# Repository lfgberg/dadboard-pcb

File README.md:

# This has not yet been tested, and firmware has not yet been pushed to qmk/via, pcb may or may not function as intended

# Dadboard PCB

PCB designed for [enwash](https://github.com/enwash) and [tesla.tech's]() [Dadboard]() Split 75%

## Renders

## Production

Download the [latest release of the production files](https://github.com/lfgberg/dadboard-pcb/releases), and submit them to a PCB manufacturer like JLCPCB or PCBWay.

## Assembly

Required:
* 1x EC11 Alps Rotary Encoder
* 2x TRRS-PJ-320A Ports

Optional:
* 92 Kailh hotswap sockets

## Author
[Lfgberg](https://github.com/lfgberg)
<br>

## License
[Attribution-NonCommercial-ShareAlike 4.0 International](https://creativecommons.org/licenses/by-nc-sa/4.0/)

This is not available for commercial use, contact [Lfgberg](https://github.com/lfgberg) for more information.

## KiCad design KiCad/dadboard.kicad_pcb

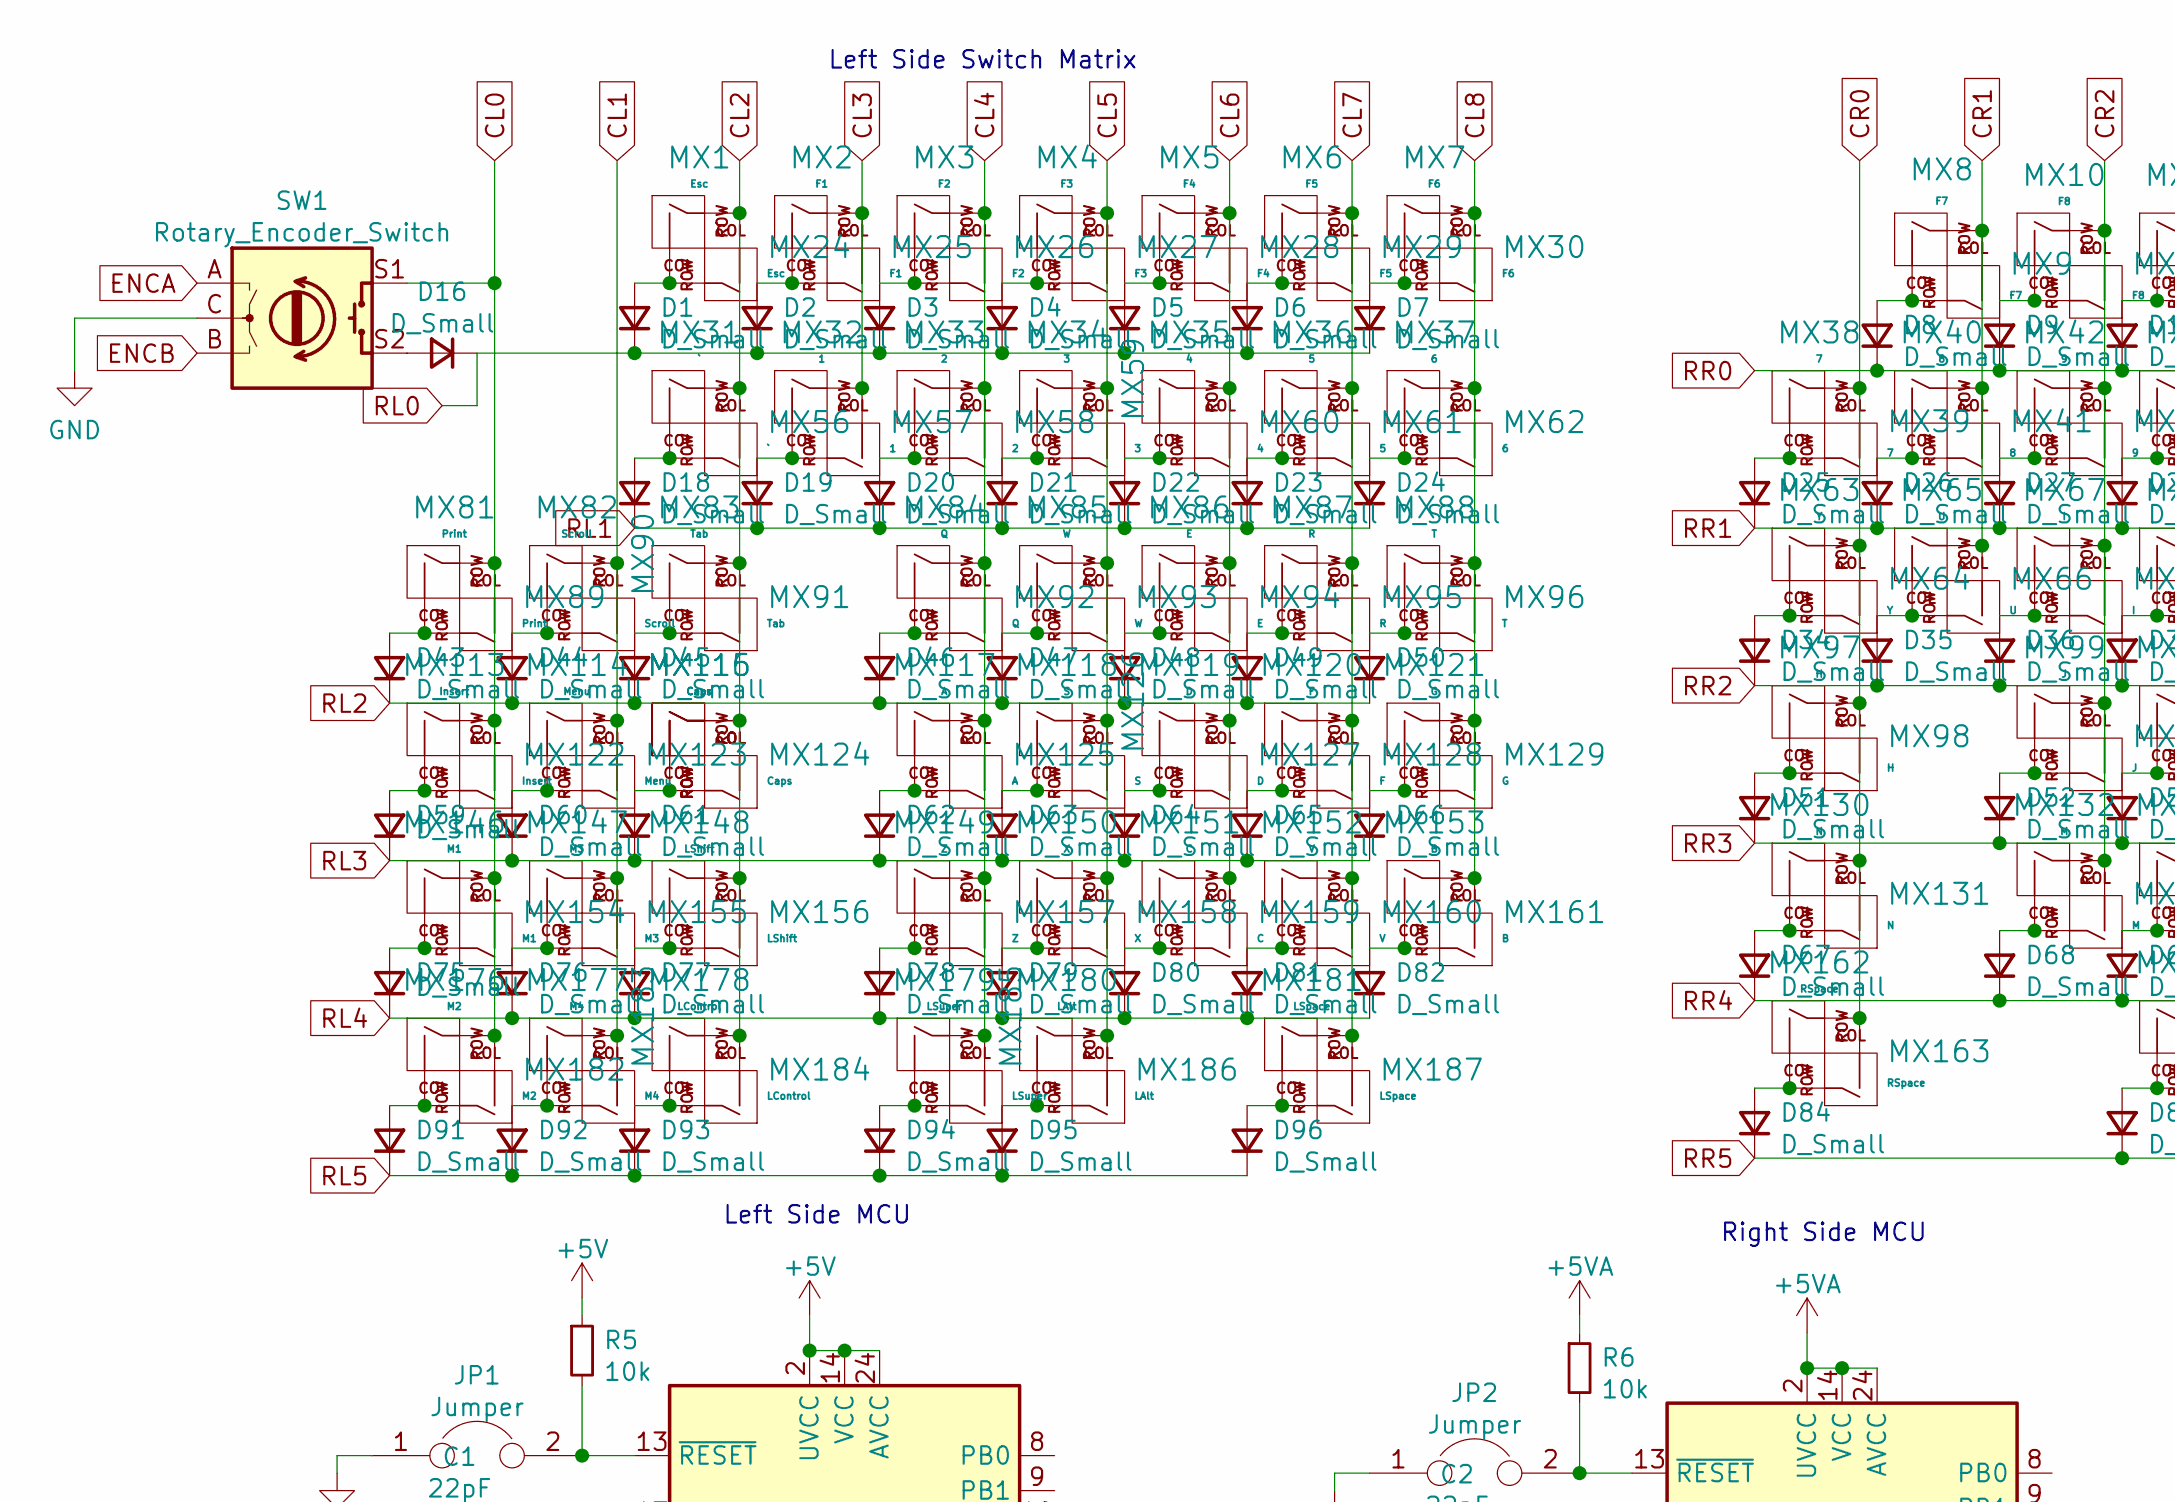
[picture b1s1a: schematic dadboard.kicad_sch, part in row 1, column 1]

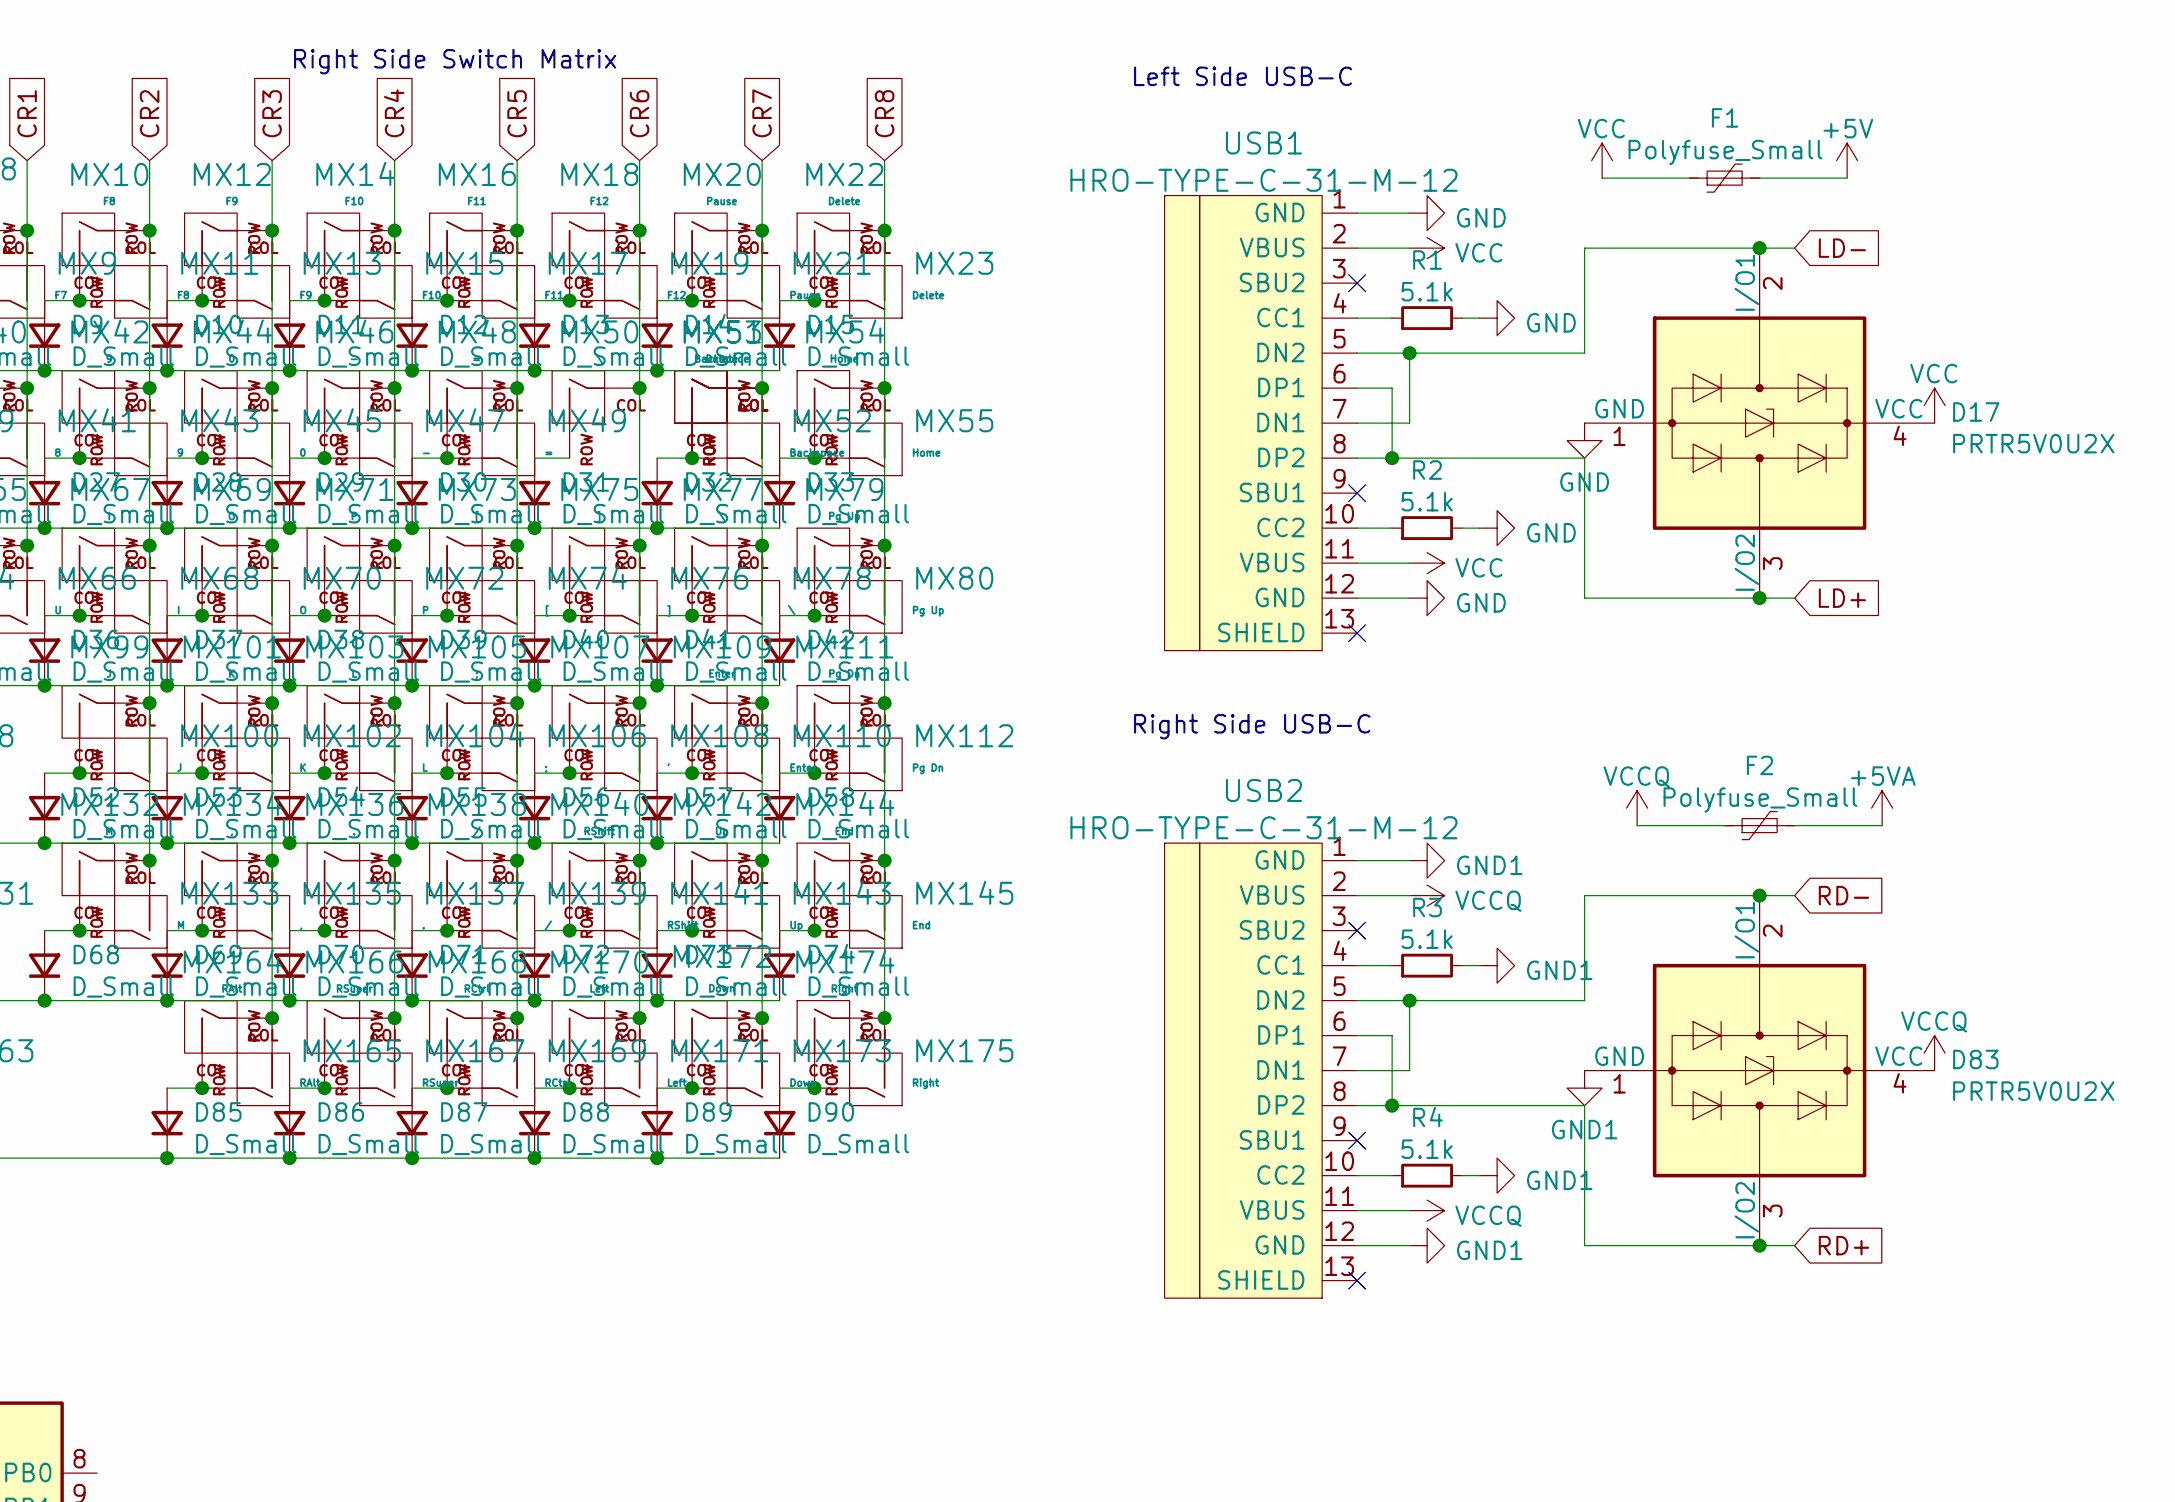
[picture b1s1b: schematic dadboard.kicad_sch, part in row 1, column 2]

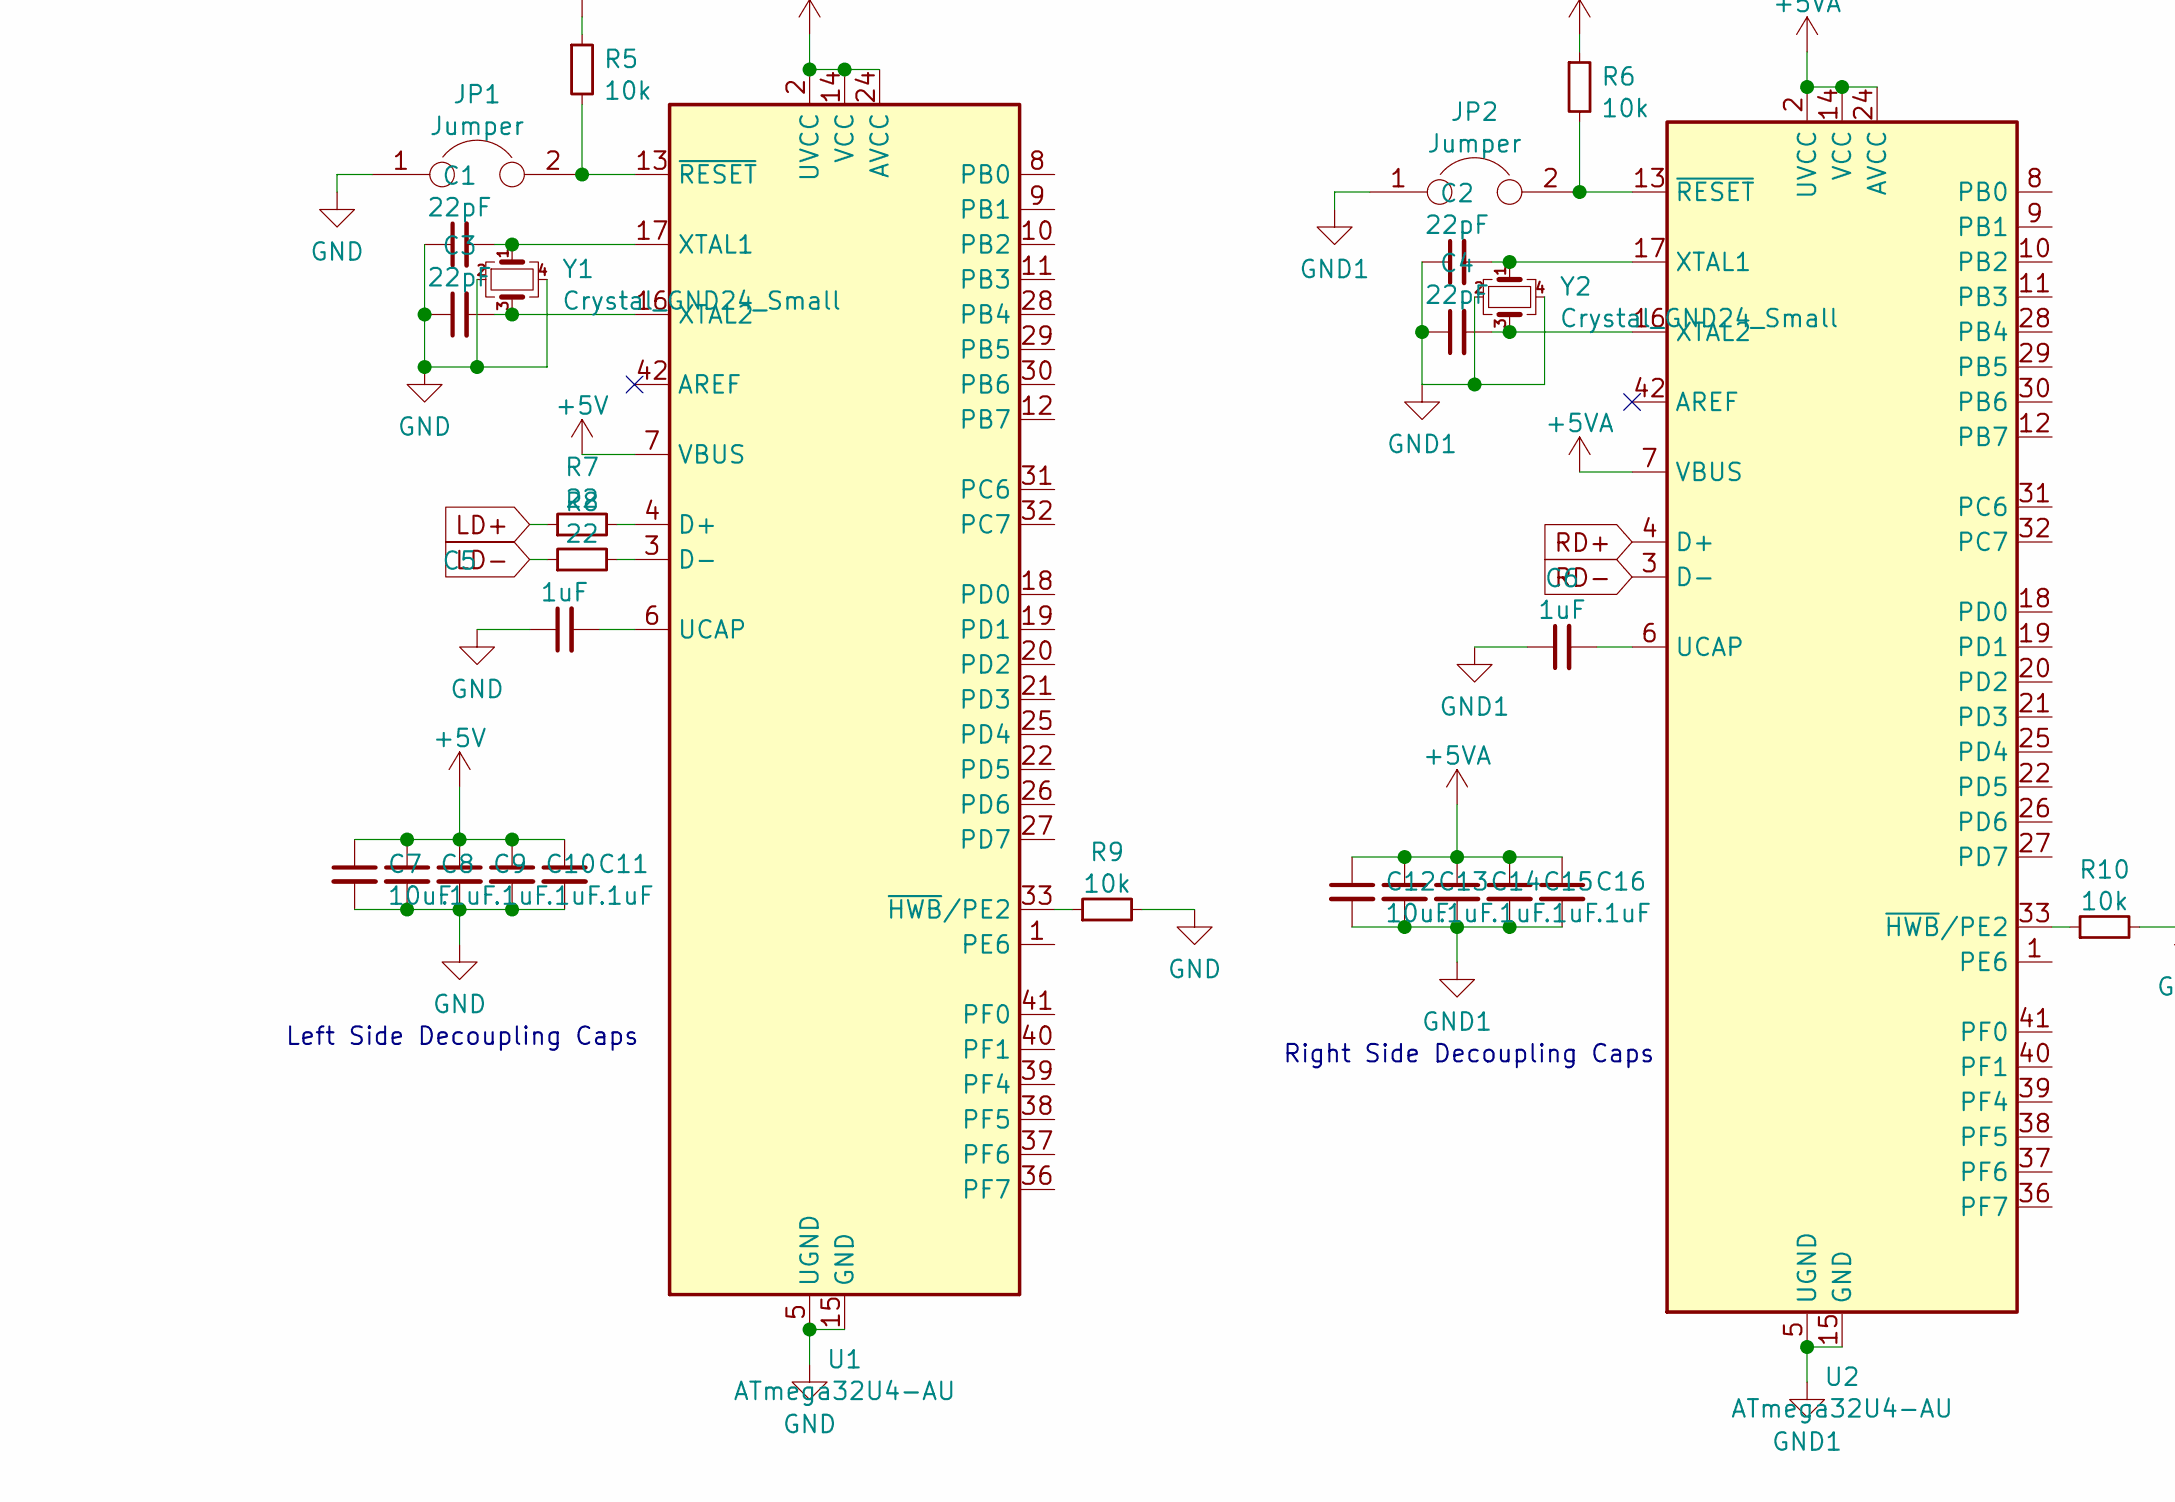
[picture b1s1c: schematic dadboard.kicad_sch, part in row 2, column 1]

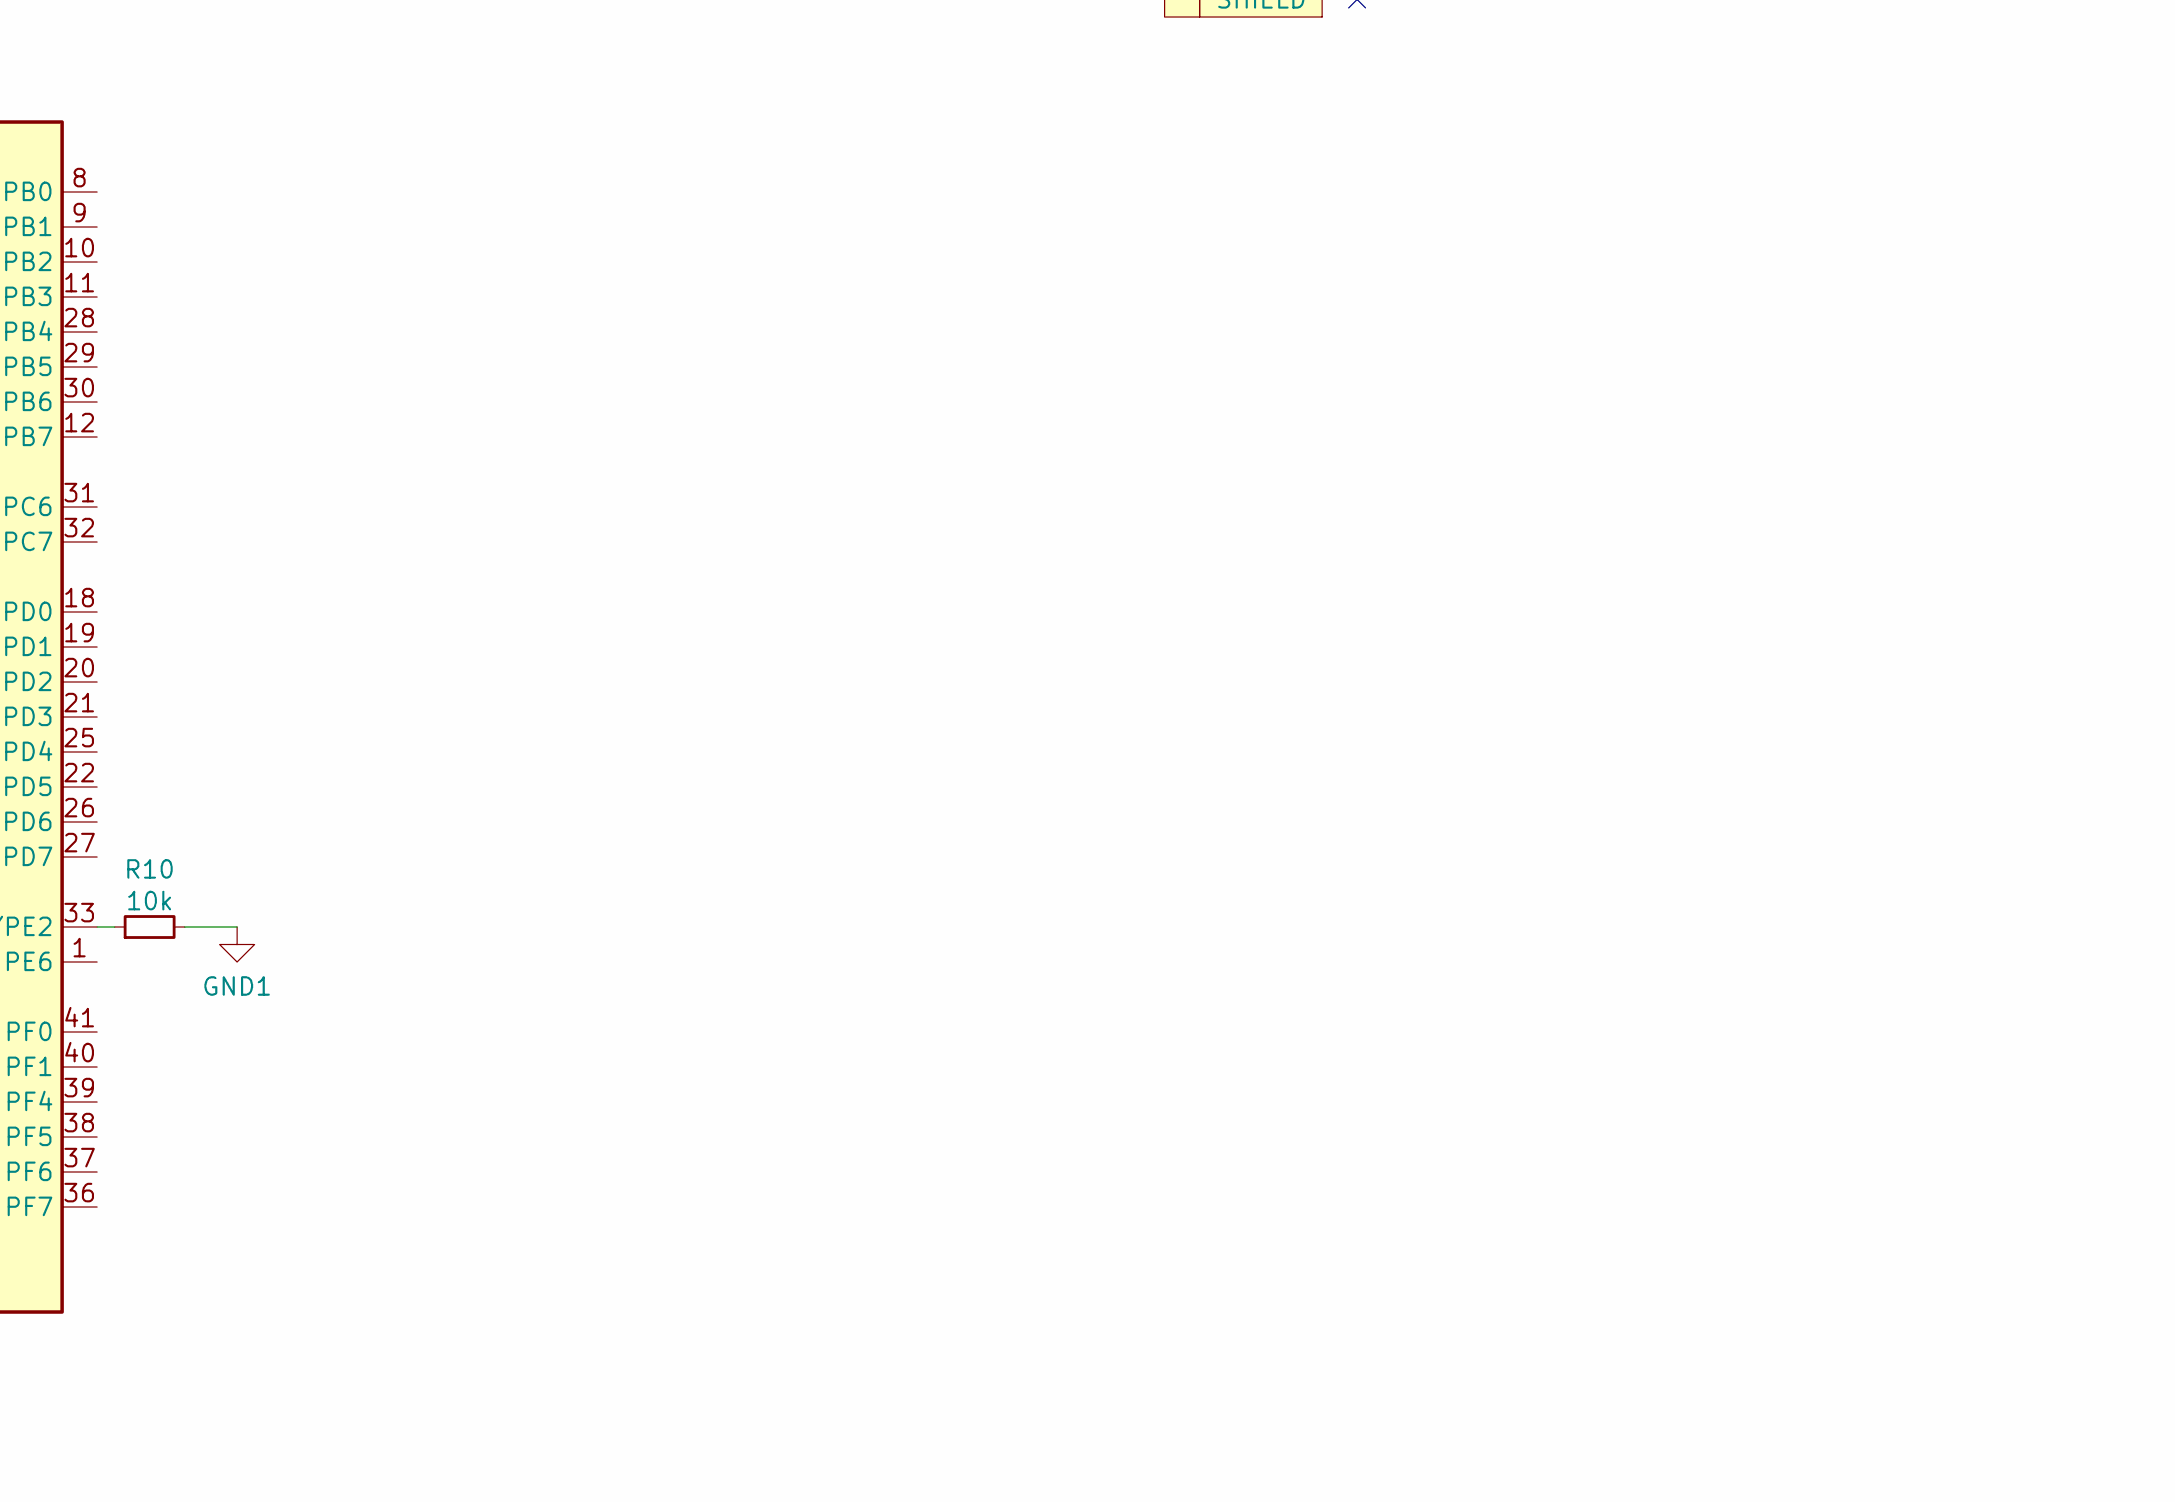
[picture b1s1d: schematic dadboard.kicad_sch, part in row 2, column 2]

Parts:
C1, C2, C3, C4: 22pF; C_0805_2012Metric
C5, C6: 1uF; C_0805_2012Metric
C7, C12: 10uF; C_0805_2012Metric
C8, C9, C10, C11, C13, C14, C15, C16: .1uF; C_0805_2012Metric
D1, D2, D3, D4, D5, D6, D7, D8, D9, D10, D11, D12, D13, D14, D15, D16, D18, D19, D20, D21, D22, D23, D24, D25, D26, D27, D28, D29, D30, D31, D32, D33, D34, D35, D36, D37, D38, D39, D40, D41, D42, D43, D44, D45, D46, D47, D48, D49, D50, D51, D52, D53, D54, D55, D56, D57, D58, D59, D60, D61, D62, D63, D64, D65, D66, D67, D68, D69, D70, D71, D72, D73, D74, D75, D76, D77, D78, D79, D80, D81, D82, D84, D85, D86, D87, D88, D89, D90, D91, D92, D93, D94, D95, D96: D_Small; D_SOD-123-Pretty
D17, D83: PRTR5V0U2X; SOT-143
F1, F2: Polyfuse_Small; Fuse_0805_2012Metric
JP1, JP2: Jumper; ResetJumper
MX1: Esc; MXOnly-1U-NoLED
MX2: F1; MXOnly-1U-NoLED
MX3: F2; MXOnly-1U-NoLED
MX4: F3; MXOnly-1U-NoLED
MX5: F4; MXOnly-1U-NoLED
MX6: F5; MXOnly-1U-NoLED
MX7: F6; MXOnly-1U-NoLED
MX8: F7; MXOnly-1U-NoLED
MX9: F7; MXOnly-1U-Hotswap
MX10: F8; MXOnly-1U-NoLED
MX11: F8; MXOnly-1U-Hotswap
MX12: F9; MXOnly-1U-NoLED
MX13: F9; MXOnly-1U-Hotswap
MX14: F10; MXOnly-1U-NoLED
MX15: F10; MXOnly-1U-Hotswap
MX16: F11; MXOnly-1U-NoLED
MX17: F11; MXOnly-1U-Hotswap
MX18: F12; MXOnly-1U-NoLED
MX19: F12; MXOnly-1U-Hotswap
MX20: Pause; MXOnly-1U-NoLED
MX21: Pause; MXOnly-1U-Hotswap
MX22, MX53: Delete; MXOnly-1U-NoLED
MX23: Delete; MXOnly-1U-Hotswap
MX24: Esc; MXOnly-1U-Hotswap
MX25: F1; MXOnly-1U-Hotswap
MX26: F2; MXOnly-1U-Hotswap
MX27: F3; MXOnly-1U-Hotswap
MX28: F4; MXOnly-1U-Hotswap
MX29: F5; MXOnly-1U-Hotswap
MX30: F6; MXOnly-1U-Hotswap
MX31: `; MXOnly-1U-NoLED
MX32: 1; MXOnly-1U-NoLED
MX33: 2; MXOnly-1U-NoLED
MX34: 3; MXOnly-1U-NoLED
MX35: 4; MXOnly-1U-NoLED
MX36: 5; MXOnly-1U-NoLED
MX37: 6; MXOnly-1U-NoLED
MX38: 7; MXOnly-1U-NoLED
MX39: 7; MXOnly-1U-Hotswap
MX40: 8; MXOnly-1U-NoLED
MX41: 8; MXOnly-1U-Hotswap
MX42: 9; MXOnly-1U-NoLED
MX43: 9; MXOnly-1U-Hotswap
MX44: 0; MXOnly-1U-NoLED
MX45: 0; MXOnly-1U-Hotswap
MX46: -; MXOnly-1U-NoLED
MX47: -; MXOnly-1U-Hotswap
MX48: =; MXOnly-1U-NoLED
MX49: =; MXOnly-1U-Hotswap
MX50: \; MXOnly-1U-NoLED
MX51: Backspace; MXOnly-2U-NoLED
MX52: Backspace; MXOnly-2U-Hotswap
MX54: Home; MXOnly-1U-NoLED
MX55: Home; MXOnly-1U-Hotswap
MX56: `; MXOnly-1U-Hotswap
MX57: 1; MXOnly-1U-Hotswap
MX58: 2; MXOnly-1U-Hotswap
MX59: 3; MXOnly-1U-Hotswap
MX60: 4; MXOnly-1U-Hotswap
MX61: 5; MXOnly-1U-Hotswap
MX62: 6; MXOnly-1U-Hotswap
MX63: Y; MXOnly-1U-NoLED
MX64: Y; MXOnly-1U-Hotswap
MX65: U; MXOnly-1U-NoLED
MX66: U; MXOnly-1U-Hotswap
MX67: I; MXOnly-1U-NoLED
MX68: I; MXOnly-1U-Hotswap
MX69: O; MXOnly-1U-NoLED
MX70: O; MXOnly-1U-Hotswap
MX71: P; MXOnly-1U-NoLED
MX72: P; MXOnly-1U-Hotswap
MX73: [; MXOnly-1U-NoLED
MX74: [; MXOnly-1U-Hotswap
MX75: ]; MXOnly-1U-NoLED
MX76: ]; MXOnly-1U-Hotswap
MX77: \; MXOnly-1.5U-NoLED
MX78: \; MXOnly-1.5U-Hotswap
MX79: Pg Up; MXOnly-1U-NoLED
MX80: Pg Up; MXOnly-1U-Hotswap
MX81: Print; MXOnly-1U-NoLED
MX82: Scroll; MXOnly-1U-NoLED
MX83: Tab; MXOnly-1.5U-NoLED
MX84: Q; MXOnly-1U-NoLED
MX85: W; MXOnly-1U-NoLED
MX86: E; MXOnly-1U-NoLED
MX87: R; MXOnly-1U-NoLED
MX88: T; MXOnly-1U-NoLED
MX89: Print; MXOnly-1U-Hotswap
MX90: Scroll; MXOnly-1U-Hotswap
MX91: Tab; MXOnly-1.5U-Hotswap
MX92: Q; MXOnly-1U-Hotswap
MX93: W; MXOnly-1U-Hotswap
MX94: E; MXOnly-1U-Hotswap
MX95: R; MXOnly-1U-Hotswap
MX96: T; MXOnly-1U-Hotswap
MX97: H; MXOnly-1U-NoLED
MX98: H; MXOnly-1U-Hotswap
MX99: J; MXOnly-1U-NoLED
MX100: J; MXOnly-1U-Hotswap
MX101: K; MXOnly-1U-NoLED
MX102: K; MXOnly-1U-Hotswap
MX103: L; MXOnly-1U-NoLED
MX104: L; MXOnly-1U-Hotswap
MX105: ;; MXOnly-1U-NoLED
MX106: ;; MXOnly-1U-Hotswap
MX107: '; MXOnly-1U-NoLED
MX108: '; MXOnly-1U-Hotswap
MX109: Enter; MXOnly-2.25U-NoLED
MX110: Enter; MXOnly-2.25U-Hotswap
MX111: Pg Dn; MXOnly-1U-NoLED
MX112: Pg Dn; MXOnly-1U-Hotswap
MX113: Insert; MXOnly-1U-NoLED
MX114: Menu; MXOnly-1U-NoLED
MX115: Caps; MXOnly-1.75U-NoLED
MX116: Caps; MXOnly-1.25U-NoLED
MX117: A; MXOnly-1U-NoLED
MX118: S; MXOnly-1U-NoLED
MX119: D; MXOnly-1U-NoLED
MX120: F; MXOnly-1U-NoLED
MX121: G; MXOnly-1U-NoLED
MX122: Insert; MXOnly-1U-Hotswap
MX123: Menu; MXOnly-1U-Hotswap
MX124: Caps; MXOnly-1.75U-Hotswap
MX125: A; MXOnly-1U-Hotswap
MX126: S; MXOnly-1U-Hotswap
MX127: D; MXOnly-1U-Hotswap
MX128: F; MXOnly-1U-Hotswap
MX129: G; MXOnly-1U-Hotswap
MX130: N; MXOnly-1U-NoLED
MX131: N; MXOnly-1U-Hotswap
MX132: M; MXOnly-1U-NoLED
MX133: M; MXOnly-1U-Hotswap
MX134: ,; MXOnly-1U-NoLED
MX135: ,; MXOnly-1U-Hotswap
MX136: .; MXOnly-1U-NoLED
MX137: .; MXOnly-1U-Hotswap
MX138: /; MXOnly-1U-NoLED
MX139: /; MXOnly-1U-Hotswap
MX140: RShift; MXOnly-1.75U-NoLED
MX141: RShift; MXOnly-1.75U-Hotswap
MX142: Up; MXOnly-1U-NoLED
MX143: Up; MXOnly-1U-Hotswap
MX144: End; MXOnly-1U-NoLED
MX145: End; MXOnly-1U-Hotswap
MX146: M1; MXOnly-1U-NoLED
MX147: M3; MXOnly-1U-NoLED
MX148: LShift; MXOnly-2.25U-NoLED
MX149: Z; MXOnly-1U-NoLED
MX150: X; MXOnly-1U-NoLED
MX151: C; MXOnly-1U-NoLED
MX152: V; MXOnly-1U-NoLED
MX153: B; MXOnly-1U-NoLED
MX154: M1; MXOnly-1U-Hotswap
MX155: M3; MXOnly-1U-Hotswap
MX156: LShift; MXOnly-2.25U-Hotswap
MX157: Z; MXOnly-1U-Hotswap
MX158: X; MXOnly-1U-Hotswap
MX159: C; MXOnly-1U-Hotswap
MX160: V; MXOnly-1U-Hotswap
MX161: B; MXOnly-1U-Hotswap
MX162: RSpace; MXOnly-3U-ReversedStabilizers-NoLED
MX163: RSpace; MXOnly-1U-Hotswap
MX164: RAlt; MXOnly-1U-NoLED
MX165: RAlt; MXOnly-1U-Hotswap
MX166: RSuper; MXOnly-1U-NoLED
MX167: RSuper; MXOnly-1U-Hotswap
MX168: RCtrl; MXOnly-1U-NoLED
MX169: RCtrl; MXOnly-1U-Hotswap
MX170: Left; MXOnly-1U-NoLED
MX171: Left; MXOnly-1U-Hotswap
MX172: Down; MXOnly-1U-NoLED
MX173: Down; MXOnly-1U-Hotswap
MX174: Right; MXOnly-1U-NoLED
MX175: Right; MXOnly-1U-Hotswap
MX176: M2; MXOnly-1U-NoLED
MX177: M4; MXOnly-1U-NoLED
MX178: LControl; MXOnly-1.5U-NoLED
MX179: LSuper; MXOnly-1U-NoLED
MX180: LAlt; MXOnly-1.5U-NoLED
MX181: LSpace; MXOnly-3U-ReversedStabilizers-NoLED
MX182: M2; MXOnly-1U-Hotswap
MX183: M4; MXOnly-1U-Hotswap
MX184: LControl; MXOnly-1.5U-Hotswap
MX185: LSuper; MXOnly-1U-Hotswap
MX186: LAlt; MXOnly-1.5U-Hotswap
MX187: LSpace; MXOnly-1U-Hotswap
R1, R2, R3, R4: 5.1k; R_0805_2012Metric
R5, R6, R9, R10: 10k; R_0805_2012Metric
R7, R8: 22; R_0805_2012Metric
SW1: Rotary_Encoder_Switch; RotaryEncoder_Alps_EC11E-Switch_Vertical_H20mm
U1, U2: ATmega32U4-AU; QFN_TQFP-44_Combined
USB1, USB2: HRO-TYPE-C-31-M-12
Y1, Y2: Crystal_GND24_Small; Crystal_SMD_3225-4Pin_3.2x2.5mm_HandSoldering

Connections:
+5V: C7.1, C8.1, C9.1, C10.1, C11.1, F1.2, R5.1, U1.2 (UVCC), U1.7 (VBUS), U1.14 (VCC), U1.24 (AVCC), U1.34 (VCC), U1.44 (AVCC)
+5VA: C12.1, C13.1, C14.1, C15.1, C16.1, F2.2, R6.1, U2.2 (UVCC), U2.7 (VBUS), U2.14 (VCC), U2.24 (AVCC), U2.34 (VCC), U2.44 (AVCC)
CL0: MX81.1 (COL), MX89.2 (ROW), MX113.1 (COL), MX122.2 (ROW), MX146.1 (COL), MX154.2 (ROW), MX176.1 (COL), MX182.2 (ROW), SW1.S1
CL1: MX82.1 (COL), MX90.2 (ROW), MX114.1 (COL), MX123.2 (ROW), MX147.1 (COL), MX155.2 (ROW), MX177.1 (COL), MX183.2 (ROW)
CL2: MX1.1 (COL), MX24.2 (ROW), MX31.1 (COL), MX56.2 (ROW), MX83.1 (COL), MX91.2 (ROW), MX115.1 (COL), MX116.1 (COL), MX124.2 (ROW), MX148.1 (COL), MX156.2 (ROW), MX178.1 (COL), MX184.2 (ROW)
CL3: MX2.1 (COL), MX25.2 (ROW), MX32.1 (COL), MX57.2 (ROW)
CL4: MX3.1 (COL), MX26.2 (ROW), MX33.1 (COL), MX58.2 (ROW), MX84.1 (COL), MX92.2 (ROW), MX117.1 (COL), MX125.2 (ROW), MX149.1 (COL), MX157.2 (ROW), MX179.1 (COL), MX185.2 (ROW)
CL5: MX4.1 (COL), MX27.2 (ROW), MX34.1 (COL), MX59.2 (ROW), MX85.1 (COL), MX93.2 (ROW), MX118.1 (COL), MX126.2 (ROW), MX150.1 (COL), MX158.2 (ROW), MX180.1 (COL), MX186.2 (ROW)
CL6: MX5.1 (COL), MX28.2 (ROW), MX35.1 (COL), MX60.2 (ROW), MX86.1 (COL), MX94.2 (ROW), MX119.1 (COL), MX127.2 (ROW), MX151.1 (COL), MX159.2 (ROW)
CL7: MX6.1 (COL), MX29.2 (ROW), MX36.1 (COL), MX61.2 (ROW), MX87.1 (COL), MX95.2 (ROW), MX120.1 (COL), MX128.2 (ROW), MX152.1 (COL), MX160.2 (ROW), MX181.1 (COL), MX187.2 (ROW)
CL8: MX7.1 (COL), MX30.2 (ROW), MX37.1 (COL), MX62.2 (ROW), MX88.1 (COL), MX96.2 (ROW), MX121.1 (COL), MX129.2 (ROW), MX153.1 (COL), MX161.2 (ROW)
CR0: MX38.1 (COL), MX39.2 (ROW), MX63.1 (COL), MX64.2 (ROW), MX97.1 (COL), MX98.2 (ROW), MX130.1 (COL), MX131.2 (ROW), MX162.1 (COL), MX163.2 (ROW)
CR1: MX8.1 (COL), MX9.2 (ROW), MX40.1 (COL), MX41.2 (ROW), MX65.1 (COL), MX66.2 (ROW)
CR3: MX12.1 (COL), MX13.2 (ROW), MX44.1 (COL), MX45.2 (ROW), MX69.1 (COL), MX70.2 (ROW), MX101.1 (COL), MX102.2 (ROW), MX134.1 (COL), MX135.2 (ROW), MX164.1 (COL), MX165.2 (ROW)
CR4: MX14.1 (COL), MX15.2 (ROW), MX46.1 (COL), MX47.2 (ROW), MX71.1 (COL), MX72.2 (ROW), MX103.1 (COL), MX104.2 (ROW), MX136.1 (COL), MX137.2 (ROW), MX166.1 (COL), MX167.2 (ROW)
CR5: MX16.1 (COL), MX17.2 (ROW), MX48.1 (COL), MX49.2 (ROW), MX73.1 (COL), MX74.2 (ROW), MX105.1 (COL), MX106.2 (ROW), MX138.1 (COL), MX139.2 (ROW), MX168.1 (COL), MX169.2 (ROW)
CR7: MX20.1 (COL), MX21.2 (ROW), MX51.1 (COL), MX52.2 (ROW), MX53.1 (COL), MX77.1 (COL), MX78.2 (ROW), MX109.1 (COL), MX110.2 (ROW), MX142.1 (COL), MX143.2 (ROW), MX172.1 (COL), MX173.2 (ROW); also elsewhere on the board
CR8: MX22.1 (COL), MX23.2 (ROW), MX54.1 (COL), MX55.2 (ROW), MX79.1 (COL), MX80.2 (ROW), MX111.1 (COL), MX112.2 (ROW), MX144.1 (COL), MX145.2 (ROW), MX174.1 (COL), MX175.2 (ROW)
ENCA: SW1.A
ENCB: SW1.B
GND1: C2.1, C4.1, C6.1, C12.2, C13.2, C14.2, C15.2, C16.2, D83.1 (GND), JP2.1, R3.2, R4.2, R10.2, U2.5 (UGND), U2.15 (GND), U2.23 (GND), U2.35 (GND), U2.43 (GND), USB2.1 (GND), USB2.12 (GND), Y2.2, Y2.4
LD+: D17.3 (I/O2), R7.1, USB1.6 (DP1), USB1.8 (DP2)
LD-: D17.2 (I/O1), R8.1, USB1.5 (DN2), USB1.7 (DN1)
unnamed: C1.2, U1.17 (XTAL1), Y1.1
unnamed: C2.2, U2.17 (XTAL1), Y2.1
unnamed: C3.2, U1.16 (XTAL2), Y1.3
unnamed: C4.2, U2.16 (XTAL2), Y2.3
unnamed: C5.2, U1.6 (UCAP)
unnamed: C6.2, U2.6 (UCAP)
unnamed: D1.2 (A), MX1.2 (ROW), MX24.1 (COL)
unnamed: D2.2 (A), MX2.2 (ROW), MX25.1 (COL)
unnamed: D3.2 (A), MX3.2 (ROW), MX26.1 (COL)
unnamed: D4.2 (A), MX4.2 (ROW), MX27.1 (COL)
unnamed: D5.2 (A), MX5.2 (ROW), MX28.1 (COL)
unnamed: D6.2 (A), MX6.2 (ROW), MX29.1 (COL)
unnamed: D7.2 (A), MX7.2 (ROW), MX30.1 (COL)
unnamed: D8.2 (A), MX8.2 (ROW), MX9.1 (COL)
unnamed: D9.2 (A), MX10.2 (ROW), MX11.1 (COL)
unnamed: D10.2 (A), MX12.2 (ROW), MX13.1 (COL)
unnamed: D11.2 (A), MX14.2 (ROW), MX15.1 (COL)
unnamed: D12.2 (A), MX16.2 (ROW), MX17.1 (COL)
unnamed: D13.2 (A), MX18.2 (ROW), MX19.1 (COL)
unnamed: D14.2 (A), MX20.2 (ROW), MX21.1 (COL)
unnamed: D15.2 (A), MX22.2 (ROW), MX23.1 (COL)
unnamed: D16.2 (A), SW1.S2
unnamed: D18.2 (A), MX31.2 (ROW), MX56.1 (COL)
unnamed: D19.2 (A), MX32.2 (ROW), MX57.1 (COL)
unnamed: D20.2 (A), MX33.2 (ROW), MX58.1 (COL)
unnamed: D21.2 (A), MX34.2 (ROW), MX59.1 (COL)
unnamed: D22.2 (A), MX35.2 (ROW), MX60.1 (COL)
unnamed: D23.2 (A), MX36.2 (ROW), MX61.1 (COL)
unnamed: D24.2 (A), MX37.2 (ROW), MX62.1 (COL)
unnamed: D25.2 (A), MX38.2 (ROW), MX39.1 (COL)
unnamed: D26.2 (A), MX40.2 (ROW), MX41.1 (COL)
unnamed: D28.2 (A), MX44.2 (ROW), MX45.1 (COL)
unnamed: D29.2 (A), MX46.2 (ROW), MX47.1 (COL)
unnamed: D30.2 (A), MX48.2 (ROW), MX49.1 (COL)
unnamed 57: D32.2 (A), MX51.2 (ROW), MX52.1 (COL), MX53.2 (ROW); also elsewhere on the board
unnamed: D33.2 (A), MX54.2 (ROW), MX55.1 (COL)
unnamed: D34.2 (A), MX63.2 (ROW), MX64.1 (COL)
unnamed: D35.2 (A), MX65.2 (ROW), MX66.1 (COL)
unnamed: D36.2 (A), MX67.2 (ROW), MX68.1 (COL)
unnamed: D37.2 (A), MX69.2 (ROW), MX70.1 (COL)
unnamed: D38.2 (A), MX71.2 (ROW), MX72.1 (COL)
unnamed: D39.2 (A), MX73.2 (ROW), MX74.1 (COL)
unnamed: D40.2 (A), MX75.2 (ROW), MX76.1 (COL)
unnamed: D41.2 (A), MX77.2 (ROW), MX78.1 (COL)
unnamed: D42.2 (A), MX79.2 (ROW), MX80.1 (COL)
unnamed: D43.2 (A), MX81.2 (ROW), MX89.1 (COL)
unnamed: D44.2 (A), MX82.2 (ROW), MX90.1 (COL)
unnamed: D45.2 (A), MX83.2 (ROW), MX91.1 (COL)
unnamed: D46.2 (A), MX84.2 (ROW), MX92.1 (COL)
unnamed: D47.2 (A), MX85.2 (ROW), MX93.1 (COL)
unnamed: D48.2 (A), MX86.2 (ROW), MX94.1 (COL)
unnamed: D49.2 (A), MX87.2 (ROW), MX95.1 (COL)
unnamed: D50.2 (A), MX88.2 (ROW), MX96.1 (COL)
unnamed: D51.2 (A), MX97.2 (ROW), MX98.1 (COL)
unnamed: D52.2 (A), MX99.2 (ROW), MX100.1 (COL)
unnamed: D53.2 (A), MX101.2 (ROW), MX102.1 (COL)
unnamed: D54.2 (A), MX103.2 (ROW), MX104.1 (COL)
unnamed: D55.2 (A), MX105.2 (ROW), MX106.1 (COL)
unnamed: D56.2 (A), MX107.2 (ROW), MX108.1 (COL)
unnamed: D57.2 (A), MX109.2 (ROW), MX110.1 (COL)
unnamed: D58.2 (A), MX111.2 (ROW), MX112.1 (COL)
unnamed: D59.2 (A), MX113.2 (ROW), MX122.1 (COL)
unnamed: D60.2 (A), MX114.2 (ROW), MX123.1 (COL)
unnamed: D61.2 (A), MX115.2 (ROW), MX116.2 (ROW), MX124.1 (COL)
unnamed: D62.2 (A), MX117.2 (ROW), MX125.1 (COL)
unnamed: D63.2 (A), MX118.2 (ROW), MX126.1 (COL)
unnamed: D64.2 (A), MX119.2 (ROW), MX127.1 (COL)
unnamed: D65.2 (A), MX120.2 (ROW), MX128.1 (COL)
unnamed: D66.2 (A), MX121.2 (ROW), MX129.1 (COL)
unnamed: D67.2 (A), MX130.2 (ROW), MX131.1 (COL)
unnamed: D68.2 (A), MX132.2 (ROW), MX133.1 (COL)
unnamed: D69.2 (A), MX134.2 (ROW), MX135.1 (COL)
unnamed: D70.2 (A), MX136.2 (ROW), MX137.1 (COL)
unnamed: D71.2 (A), MX138.2 (ROW), MX139.1 (COL)
unnamed: D72.2 (A), MX140.2 (ROW), MX141.1 (COL)
unnamed: D73.2 (A), MX142.2 (ROW), MX143.1 (COL)
unnamed: D74.2 (A), MX144.2 (ROW), MX145.1 (COL)
unnamed: D75.2 (A), MX146.2 (ROW), MX154.1 (COL)
unnamed: D76.2 (A), MX147.2 (ROW), MX155.1 (COL)
unnamed: D77.2 (A), MX148.2 (ROW), MX156.1 (COL)
unnamed: D78.2 (A), MX149.2 (ROW), MX157.1 (COL)
unnamed: D79.2 (A), MX150.2 (ROW), MX158.1 (COL)
unnamed: D80.2 (A), MX151.2 (ROW), MX159.1 (COL)
unnamed: D81.2 (A), MX152.2 (ROW), MX160.1 (COL)
unnamed: D82.2 (A), MX153.2 (ROW), MX161.1 (COL)
unnamed: D84.2 (A), MX162.2 (ROW), MX163.1 (COL)
unnamed: D85.2 (A), MX164.2 (ROW), MX165.1 (COL)
unnamed: D86.2 (A), MX166.2 (ROW), MX167.1 (COL)
unnamed: D87.2 (A), MX168.2 (ROW), MX169.1 (COL)
unnamed: D88.2 (A), MX170.2 (ROW), MX171.1 (COL)
unnamed: D89.2 (A), MX172.2 (ROW), MX173.1 (COL)
unnamed: D90.2 (A), MX174.2 (ROW), MX175.1 (COL)
unnamed: D91.2 (A), MX176.2 (ROW), MX182.1 (COL)
unnamed: D92.2 (A), MX177.2 (ROW), MX183.1 (COL)
unnamed: D93.2 (A), MX178.2 (ROW), MX184.1 (COL)
unnamed: D94.2 (A), MX179.2 (ROW), MX185.1 (COL)
unnamed: D95.2 (A), MX180.2 (ROW), MX186.1 (COL)
unnamed: D96.2 (A), MX181.2 (ROW), MX187.1 (COL)
unnamed: JP2.2, R6.2, U2.13 (~RESET)
unnamed: R1.1, USB1.4 (CC1)
unnamed: R2.1, USB1.10 (CC2)
unnamed: R3.1, USB2.4 (CC1)
unnamed: R4.1, USB2.10 (CC2)
unnamed: R7.2, U1.4 (D+)
unnamed: R8.2, U1.3 (D-)
unnamed: R9.1, U1.33 (~HWB/PE2)
unnamed: R10.1, U2.33 (~HWB/PE2)
RD+: D83.3 (I/O2), U2.4 (D+), USB2.6 (DP1), USB2.8 (DP2)
RD-: D83.2 (I/O1), U2.3 (D-), USB2.5 (DN2), USB2.7 (DN1)
RL0: D1.1 (K), D2.1 (K), D3.1 (K), D4.1 (K), D5.1 (K), D6.1 (K), D7.1 (K), D16.1 (K)
RL1: D18.1 (K), D19.1 (K), D20.1 (K), D21.1 (K), D22.1 (K), D23.1 (K), D24.1 (K)
RL2: D43.1 (K), D44.1 (K), D45.1 (K), D46.1 (K), D47.1 (K), D48.1 (K), D49.1 (K), D50.1 (K)
RL3: D59.1 (K), D60.1 (K), D61.1 (K), D62.1 (K), D63.1 (K), D64.1 (K), D65.1 (K), D66.1 (K)
RL4: D75.1 (K), D76.1 (K), D77.1 (K), D78.1 (K), D79.1 (K), D80.1 (K), D81.1 (K), D82.1 (K)
RL5: D91.1 (K), D92.1 (K), D93.1 (K), D94.1 (K), D95.1 (K), D96.1 (K)
RR0: D8.1 (K), D9.1 (K), D10.1 (K), D11.1 (K), D12.1 (K), D13.1 (K), D14.1 (K), D15.1 (K)
RR1: D25.1 (K), D26.1 (K), D27.1 (K), D28.1 (K), D29.1 (K), D30.1 (K), D31.1 (K), D32.1 (K), D33.1 (K)
RR2: D34.1 (K), D35.1 (K), D36.1 (K), D37.1 (K), D38.1 (K), D39.1 (K), D40.1 (K), D41.1 (K), D42.1 (K)
RR3: D51.1 (K), D52.1 (K), D53.1 (K), D54.1 (K), D55.1 (K), D56.1 (K), D57.1 (K), D58.1 (K)
RR4: D67.1 (K), D68.1 (K), D69.1 (K), D70.1 (K), D71.1 (K), D72.1 (K), D73.1 (K), D74.1 (K)
RR5: D84.1 (K), D85.1 (K), D86.1 (K), D87.1 (K), D88.1 (K), D89.1 (K), D90.1 (K)
VCC: D17.4 (VCC), F1.1, USB1.2 (VBUS), USB1.11 (VBUS)
VCCQ: D83.4 (VCC), F2.1, USB2.2 (VBUS), USB2.11 (VBUS)

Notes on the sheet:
Left Side Decoupling Caps
Left Side MCU
Left Side Switch Matrix
Right Side Decoupling Caps
Right Side MCU
Right Side Switch Matrix
Left Side USB-C
Right Side USB-C

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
